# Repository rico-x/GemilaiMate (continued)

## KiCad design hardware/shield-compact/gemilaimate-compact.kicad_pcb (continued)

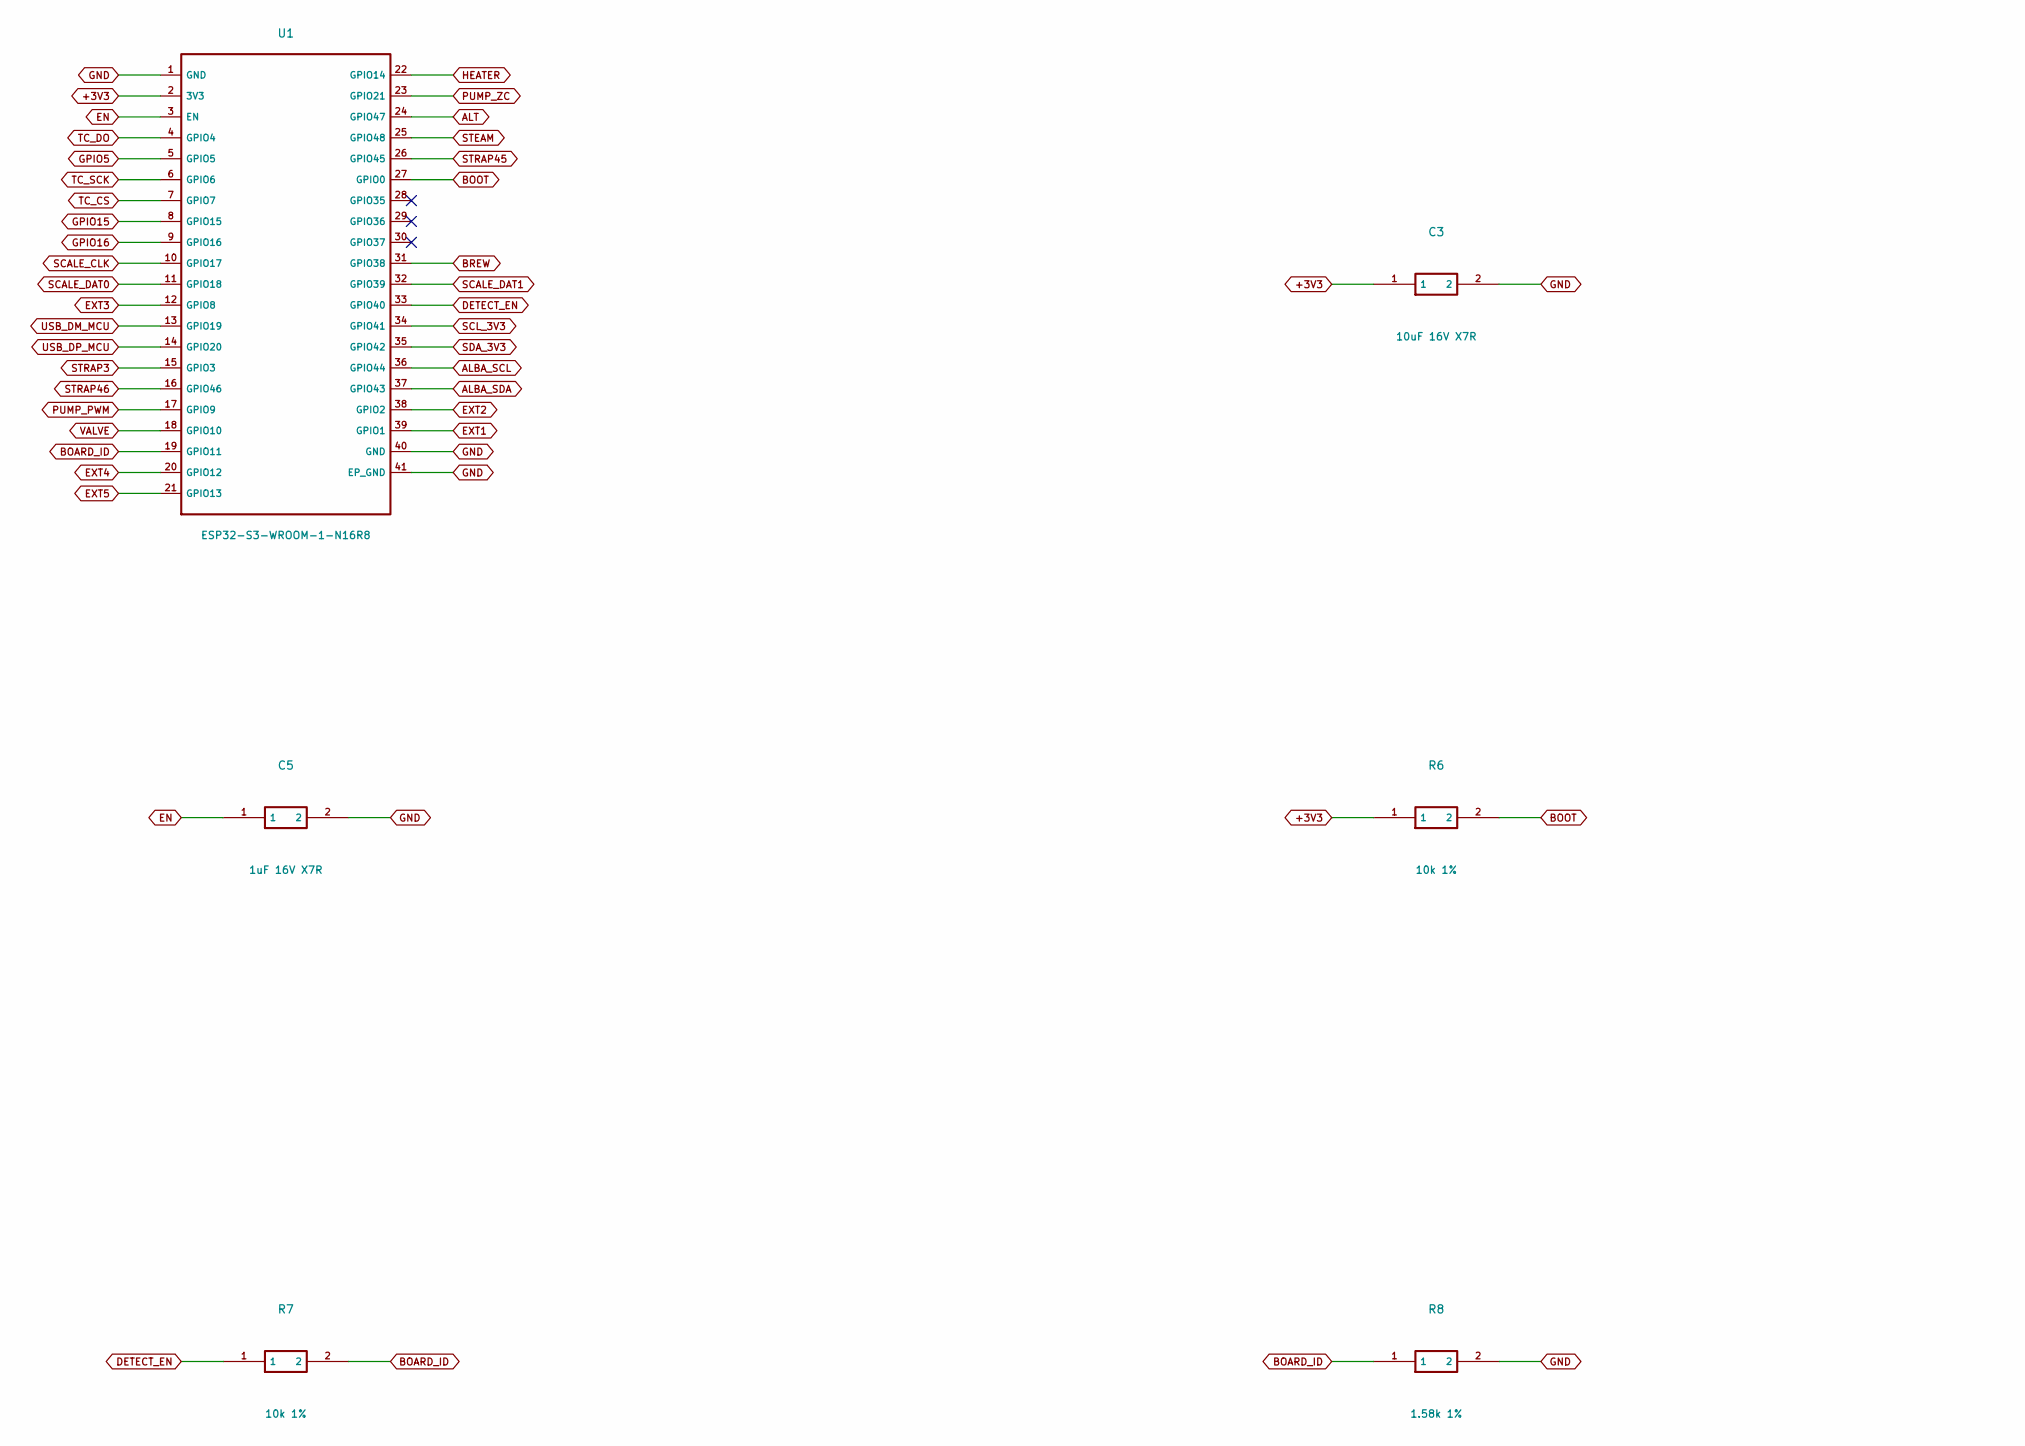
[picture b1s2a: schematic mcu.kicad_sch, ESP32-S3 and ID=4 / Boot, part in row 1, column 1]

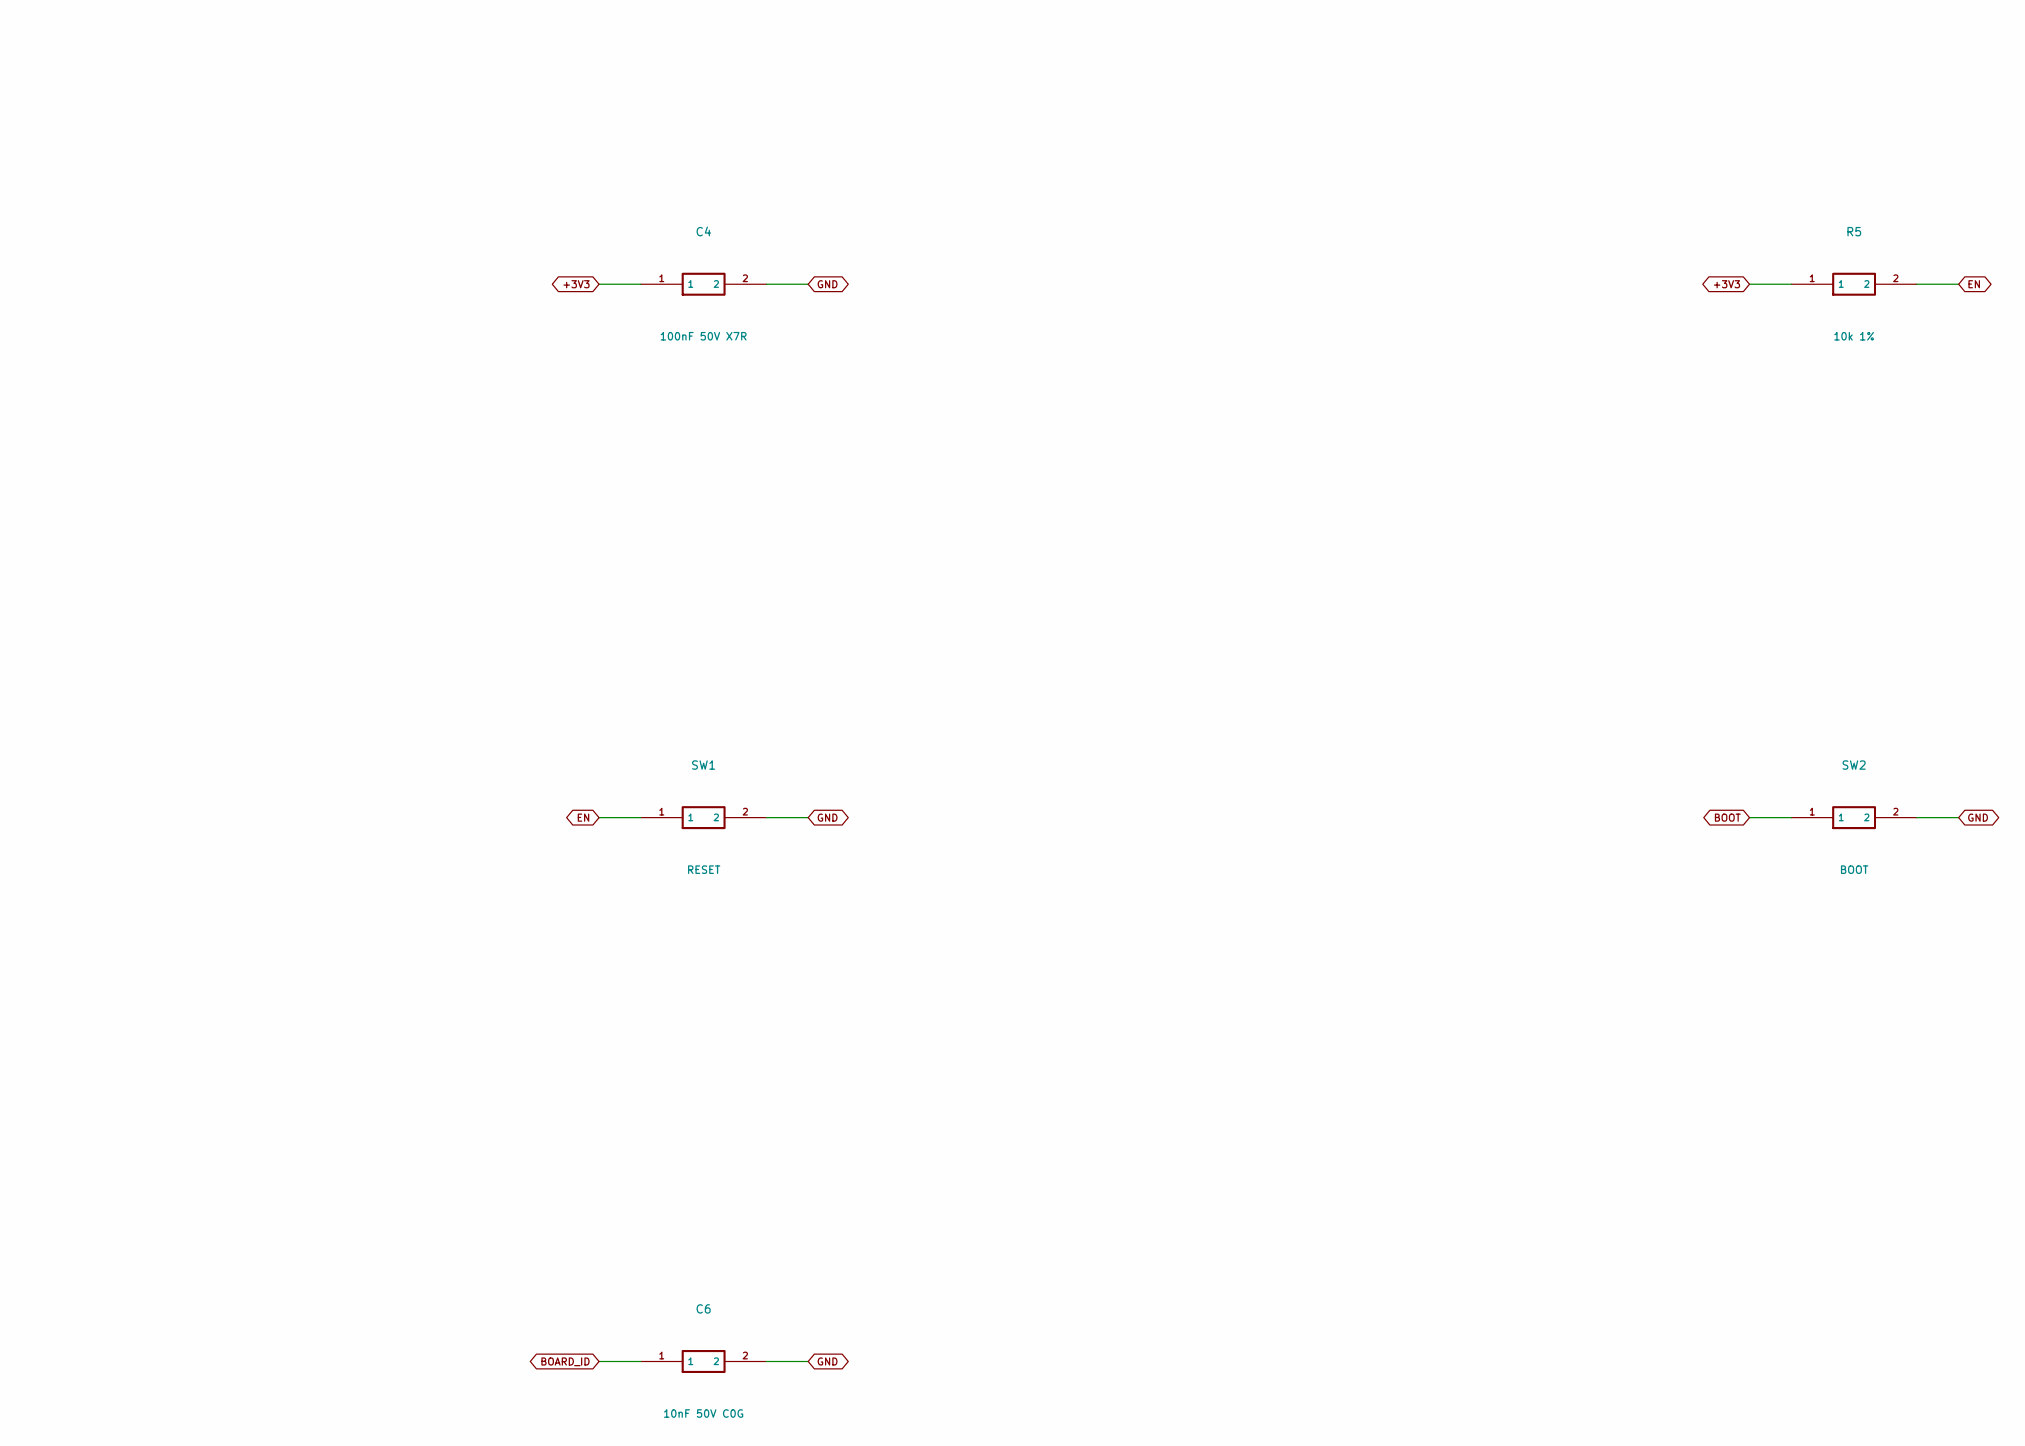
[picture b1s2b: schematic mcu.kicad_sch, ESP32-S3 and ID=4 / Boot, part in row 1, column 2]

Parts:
C3: 10uF 16V X7R; C_1206_3216Metric_Pad1.33x1.80mm_HandSolder
C4: 100nF 50V X7R; C_0805_2012Metric_Pad1.18x1.45mm_HandSolder
C5: 1uF 16V X7R; C_0805_2012Metric_Pad1.18x1.45mm_HandSolder
C6: 10nF 50V C0G; C_0805_2012Metric_Pad1.18x1.45mm_HandSolder
R5, R6, R7: 10k 1%; R_0805_2012Metric_Pad1.20x1.40mm_HandSolder
R8: 1.58k 1%; R_0805_2012Metric_Pad1.20x1.40mm_HandSolder
SW1: RESET; SW_SPST_TL3342
SW2: BOOT; SW_SPST_TL3342
U1: ESP32-S3-WROOM-1-N16R8; ESP32-S3-WROOM-1

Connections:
+3V3: C3.1, C4.1, R5.1, R6.1, U1.2 (3V3); also elsewhere on the board
ALBA_SCL: U1.36 (GPIO44); also elsewhere on the board
ALBA_SDA: U1.37 (GPIO43); also elsewhere on the board
ALT: U1.24 (GPIO47); also elsewhere on the board
BOARD_ID: C6.1, R7.2, R8.1, U1.19 (GPIO11)
BOOT: R6.2, SW2.1, U1.27 (GPIO0); also elsewhere on the board
BREW: U1.31 (GPIO38); also elsewhere on the board
DETECT_EN: R7.1, U1.33 (GPIO40)
EN: C5.1, R5.2, SW1.1, U1.3 (EN)
EXT1: U1.39 (GPIO1); also elsewhere on the board
EXT2: U1.38 (GPIO2); also elsewhere on the board
EXT3: U1.12 (GPIO8); also elsewhere on the board
EXT4: U1.20 (GPIO12); also elsewhere on the board
EXT5: U1.21 (GPIO13); also elsewhere on the board
GND: C3.2, C4.2, C5.2, C6.2, R8.2, SW1.2, SW2.2, U1.1 (GND), U1.40 (GND), U1.41 (EP_GND); also elsewhere on the board
GPIO5: U1.5 (GPIO5); also elsewhere on the board
GPIO15: U1.8 (GPIO15); also elsewhere on the board
GPIO16: U1.9 (GPIO16); also elsewhere on the board
HEATER: U1.22 (GPIO14); also elsewhere on the board
PUMP_PWM: U1.17 (GPIO9); also elsewhere on the board
PUMP_ZC: U1.23 (GPIO21); also elsewhere on the board
SCALE_CLK: U1.10 (GPIO17); also elsewhere on the board
SCALE_DAT0: U1.11 (GPIO18); also elsewhere on the board
SCALE_DAT1: U1.32 (GPIO39); also elsewhere on the board
SCL_3V3: U1.34 (GPIO41); also elsewhere on the board
SDA_3V3: U1.35 (GPIO42); also elsewhere on the board
STEAM: U1.25 (GPIO48); also elsewhere on the board
STRAP3: U1.15 (GPIO3); also elsewhere on the board
STRAP45: U1.26 (GPIO45); also elsewhere on the board
STRAP46: U1.16 (GPIO46); also elsewhere on the board
TC_CS: U1.7 (GPIO7); also elsewhere on the board
TC_DO: U1.4 (GPIO4); also elsewhere on the board
TC_SCK: U1.6 (GPIO6); also elsewhere on the board
USB_DM_MCU: U1.13 (GPIO19); also elsewhere on the board
USB_DP_MCU: U1.14 (GPIO20); also elsewhere on the board
VALVE: U1.18 (GPIO10); also elsewhere on the board

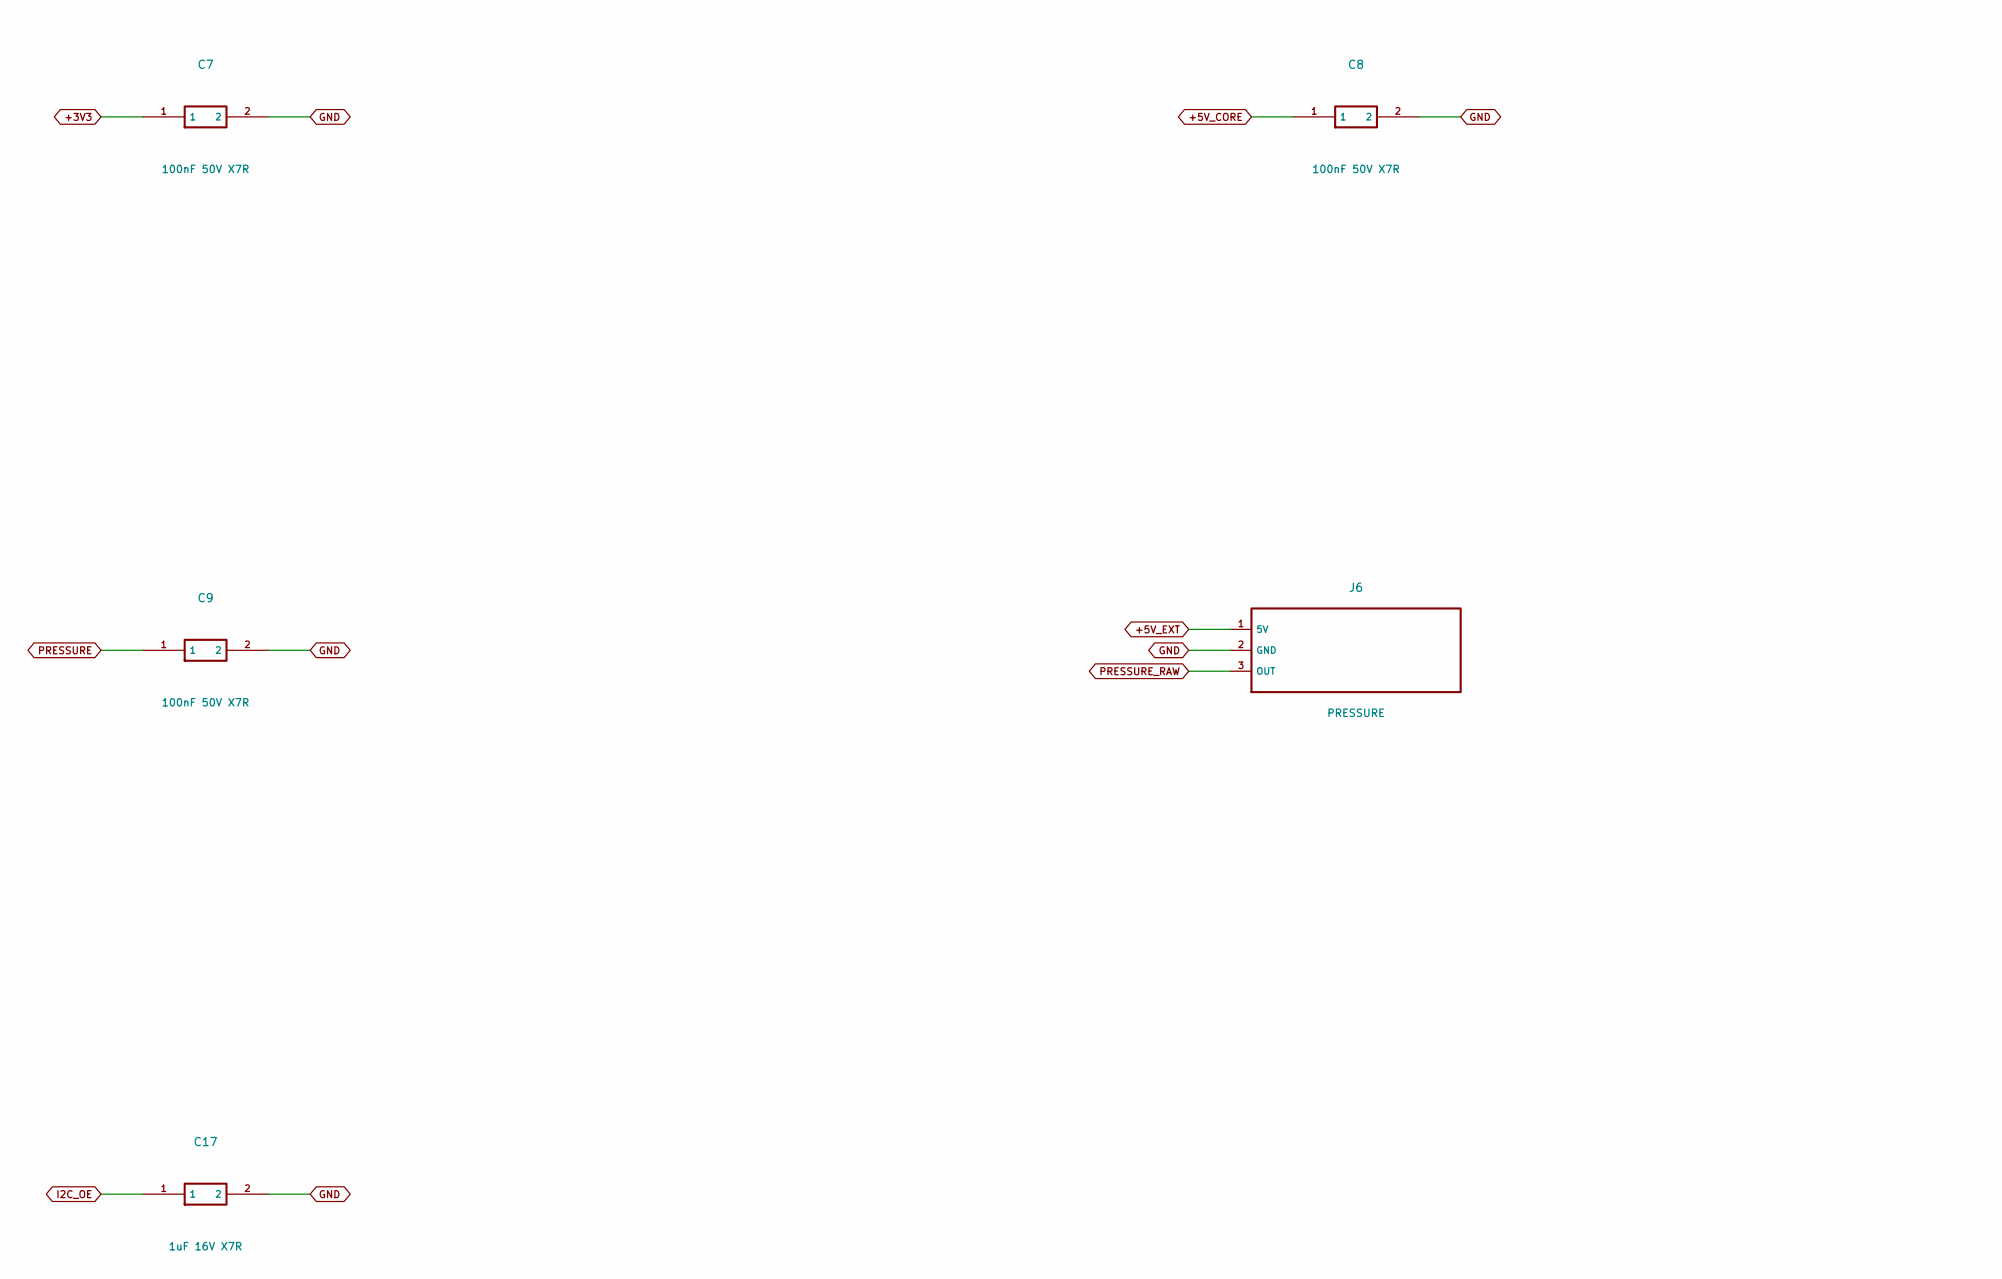
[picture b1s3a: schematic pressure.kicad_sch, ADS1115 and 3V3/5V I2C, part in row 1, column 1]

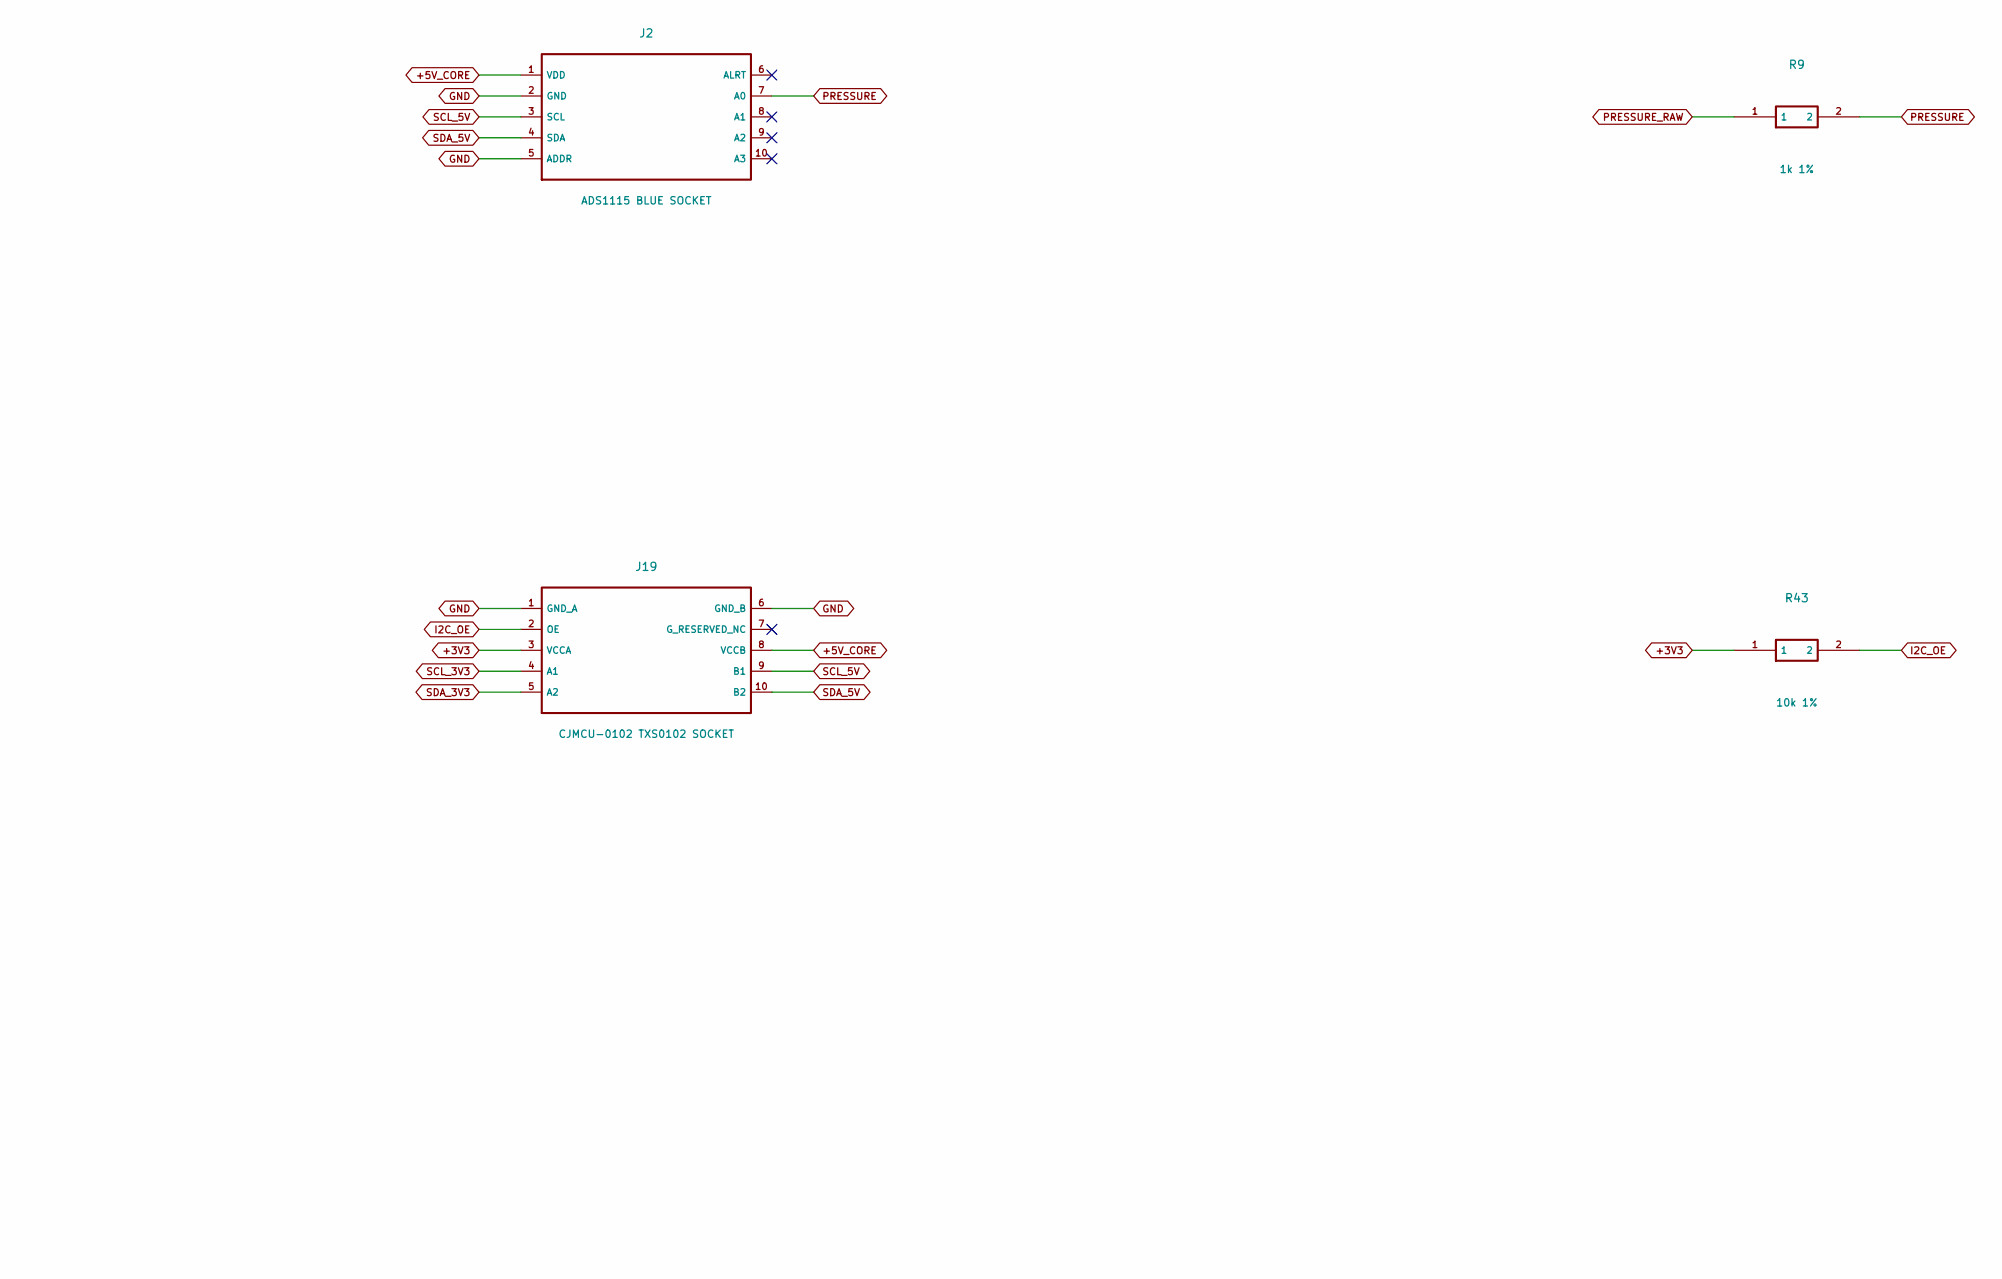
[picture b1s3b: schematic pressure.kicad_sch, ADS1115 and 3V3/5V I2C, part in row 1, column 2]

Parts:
C7, C8, C9: 100nF 50V X7R; C_0805_2012Metric_Pad1.18x1.45mm_HandSolder
C17: 1uF 16V X7R; C_0805_2012Metric_Pad1.18x1.45mm_HandSolder
J2: ADS1115 BLUE SOCKET; ADS1115_socket
J6: PRESSURE; JST_PH_B3B-PH-K_1x03_P2.00mm_Vertical
J19: CJMCU-0102 TXS0102 SOCKET; CJMCU0102_socket
R9: 1k 1%; R_0805_2012Metric_Pad1.20x1.40mm_HandSolder
R43: 10k 1%; R_0805_2012Metric_Pad1.20x1.40mm_HandSolder

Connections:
+3V3: C7.1, J19.3 (VCCA), R43.1; also elsewhere on the board
+5V_CORE: C8.1, J2.1 (VDD), J19.8 (VCCB); also elsewhere on the board
+5V_EXT: J6.1 (5V); also elsewhere on the board
GND: C7.2, C8.2, C9.2, C17.2, J2.2 (GND), J2.5 (ADDR), J6.2 (GND), J19.1 (GND_A), J19.6 (GND_B); also elsewhere on the board
I2C_OE: C17.1, J19.2 (OE), R43.2
PRESSURE: C9.1, J2.7 (A0), R9.2
PRESSURE_RAW: J6.3 (OUT), R9.1
SCL_3V3: J19.4 (A1); also elsewhere on the board
SCL_5V: J2.3 (SCL), J19.9 (B1)
SDA_3V3: J19.5 (A2); also elsewhere on the board
SDA_5V: J2.4 (SDA), J19.10 (B2)

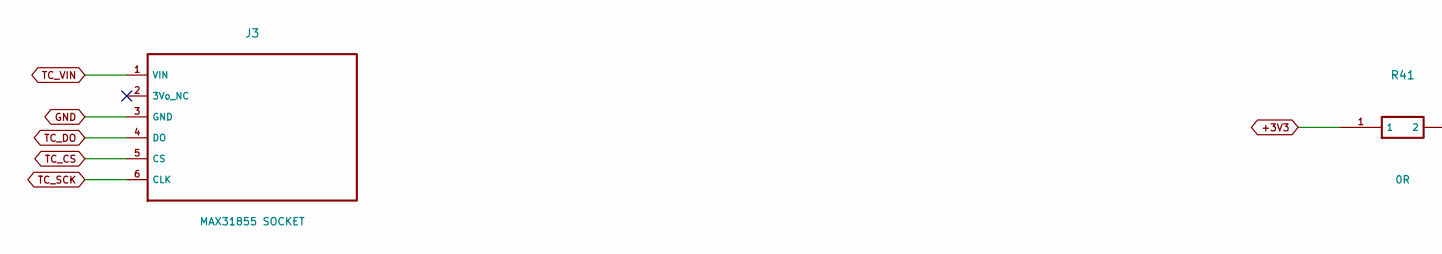
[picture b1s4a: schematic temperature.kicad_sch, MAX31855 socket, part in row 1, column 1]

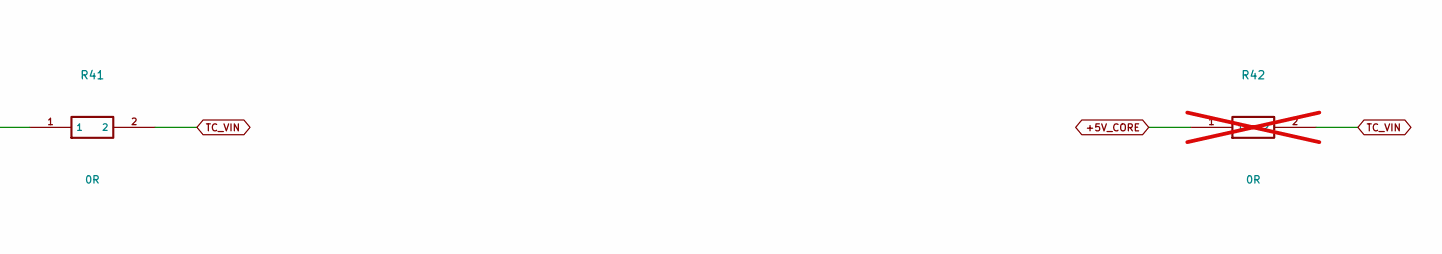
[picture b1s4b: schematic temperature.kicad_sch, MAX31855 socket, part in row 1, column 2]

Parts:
J3: MAX31855 SOCKET; MAX31855_socket
R41: 0R; R_0805_2012Metric_Pad1.20x1.40mm_HandSolder
R42: 0R; R_0805_2012Metric_Pad1.20x1.40mm_HandSolder; not fitted

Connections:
+3V3: R41.1; also elsewhere on the board
+5V_CORE: R42.1; also elsewhere on the board
GND: J3.3 (GND); also elsewhere on the board
TC_CS: J3.5 (CS); also elsewhere on the board
TC_DO: J3.4 (DO); also elsewhere on the board
TC_SCK: J3.6 (CLK); also elsewhere on the board
TC_VIN: J3.1 (VIN), R41.2, R42.2

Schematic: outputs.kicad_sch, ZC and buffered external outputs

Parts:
C10, C11, C12, C15: 100nF 50V X7R; C_0805_2012Metric_Pad1.18x1.45mm_HandSolder
J8: ROBOTDYN; JST_PH_B6B-PH-K_1x06_P2.00mm_Vertical
J9: VALVE SSR; JST_PH_B3B-PH-K_1x03_P2.00mm_Vertical
J10: HEATER UNUSED; JST_PH_B3B-PH-K_1x03_P2.00mm_Vertical; not fitted
J11: ALT SSR; JST_PH_B3B-PH-K_1x03_P2.00mm_Vertical
Q1: MMBT3904; SOT-23_Handsoldering
R10, R14, R15, R16, R17, R18, R19, R20, R21, R22: 10k 1%; R_0805_2012Metric_Pad1.20x1.40mm_HandSolder
R11: 1k 1%; R_0805_2012Metric_Pad1.20x1.40mm_HandSolder
R12: 47k 1%; R_0805_2012Metric_Pad1.20x1.40mm_HandSolder
R13, R36, R38: 100k 1%; R_0805_2012Metric_Pad1.20x1.40mm_HandSolder
R27, R28: 0R; R_0805_2012Metric_Pad1.20x1.40mm_HandSolder
R29, R30: 4.7k 1%; R_0805_2012Metric_Pad1.20x1.40mm_HandSolder
R31, R32, R33, R34: 180R 1%; R_0805_2012Metric_Pad1.20x1.40mm_HandSolder
R35, R37: 100R 1%; R_0805_2012Metric_Pad1.20x1.40mm_HandSolder
U4: SN74LVC1G17DBVR; SOT-23-5_HandSoldering
U5: SN74LVC1G125DBVR; SOT-23-5_HandSoldering
U6: SN74AHCT125DR; SOIC-14_3.9x8.7mm_P1.27mm

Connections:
+3V3: C10.1, C12.1, C15.1, R14.1, R29.1, R30.1, U4.5 (VCC), U5.5 (VCC); also elsewhere on the board
+5V_EXT: C11.1, J8.1 (5V), J9.1 (5V), J10.1 (5V), J11.1 (5V), R10.1, R12.1, U6.13 (4OE_N), U6.14 (VCC); also elsewhere on the board
ALBA_SCL: R27.1, R30.2; also elsewhere on the board
ALBA_SDA: R28.1, R29.2; also elsewhere on the board
ALT: R18.1, U6.9 (3A); also elsewhere on the board
ALT_5V: J11.3 (IN), R22.1, U6.8 (3Y)
EXT_BASE: Q1.1 (B), R12.2, R13.1
GND: C10.2, C11.2, C12.2, C15.2, J8.2 (GND), J9.2 (GND), J10.2 (GND), J11.2 (GND), Q1.2 (E), R13.2, R15.2, R16.2, R17.2, R18.2, R19.2, R20.2, R21.2, R22.2, R36.2, R38.2, U4.3 (GND), U5.3 (GND), U6.7 (GND), U6.12 (4A); also elsewhere on the board
HEATER: R17.1, U6.5 (2A); also elsewhere on the board
HEATER_5V: J10.3 (IN), R21.1, U6.6 (2Y)
LED_GATE4: R35.2, R36.1; also elsewhere on the board
LED_GATE5: R37.2, R38.1; also elsewhere on the board
OUTPUT_OE_N: Q1.3 (C), R14.2, U5.1 (OE_N), U6.1 (1OE_N), U6.4 (2OE_N), U6.10 (3OE_N)
PCA_LED0: R31.1; also elsewhere on the board
PCA_LED1: R32.1; also elsewhere on the board
PCA_LED2: R33.1; also elsewhere on the board
PCA_LED3: R34.1; also elsewhere on the board
PCA_LED4: R35.1; also elsewhere on the board
PCA_LED5: R37.1; also elsewhere on the board
PCA_SCL: R27.2; also elsewhere on the board
PCA_SDA: R28.2; also elsewhere on the board
PUMP_OUT: J8.4 (PSM), R19.1, U5.4 (Y)
PUMP_PWM: R15.1, U5.2 (A); also elsewhere on the board
PUMP_ZC: U4.4 (Y); also elsewhere on the board
RGBW0: R31.2; also elsewhere on the board
RGBW1: R32.2; also elsewhere on the board
RGBW2: R33.2; also elsewhere on the board
RGBW3: R34.2; also elsewhere on the board
VALVE: R16.1, U6.2 (1A); also elsewhere on the board
VALVE_5V: J9.3 (IN), R20.1, U6.3 (1Y)
ZC_IN: R11.2, U4.2 (A)
ZC_RAW: J8.3 (ZC), R10.2, R11.1

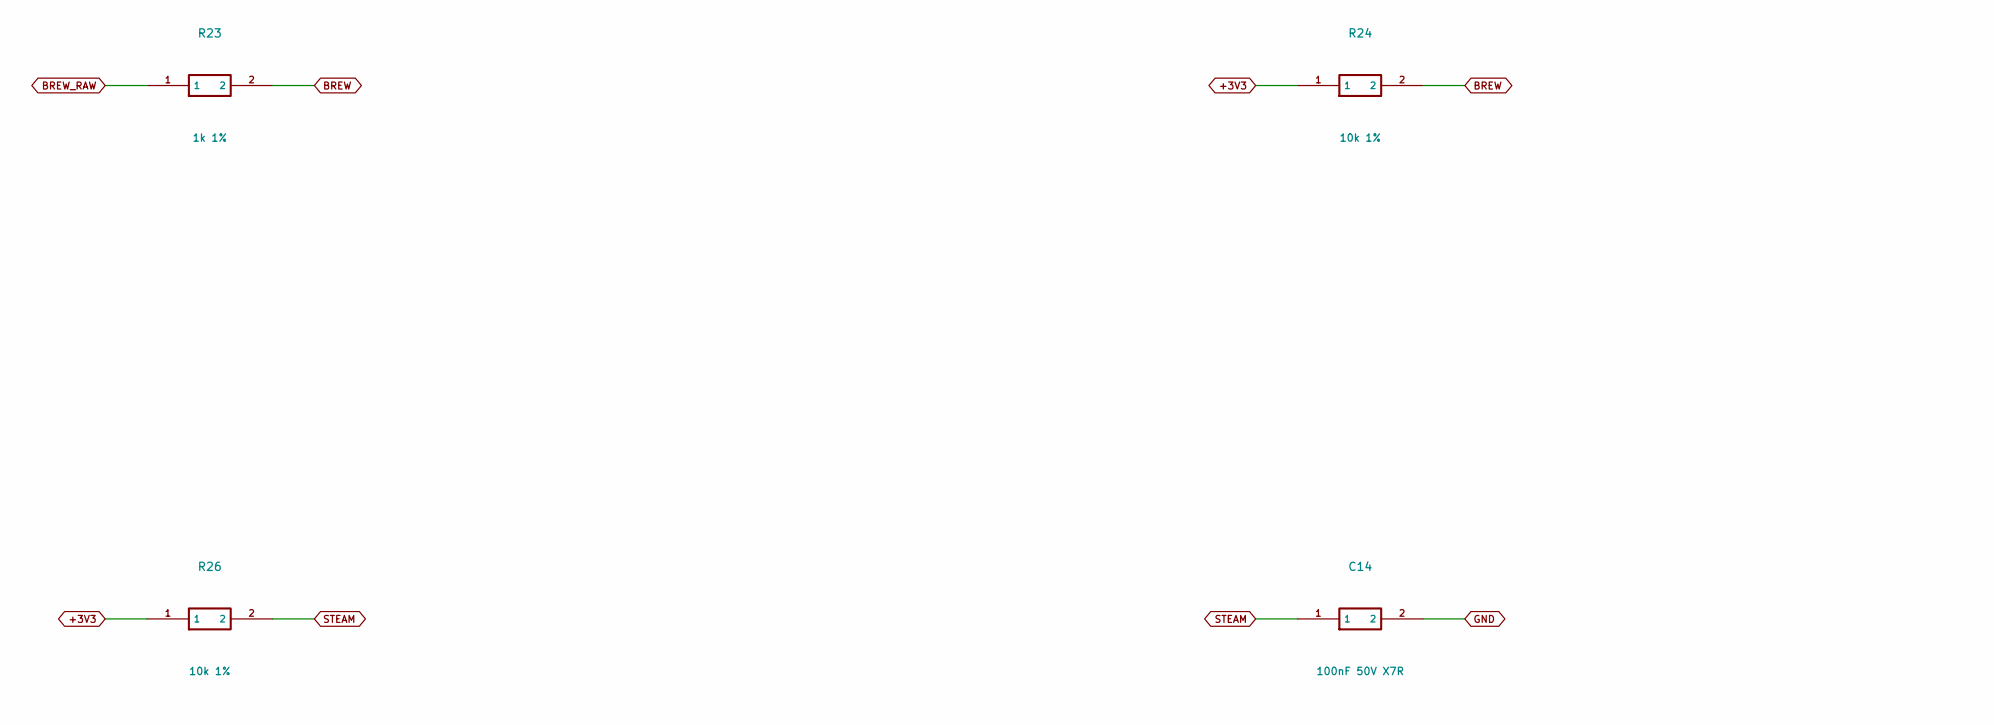
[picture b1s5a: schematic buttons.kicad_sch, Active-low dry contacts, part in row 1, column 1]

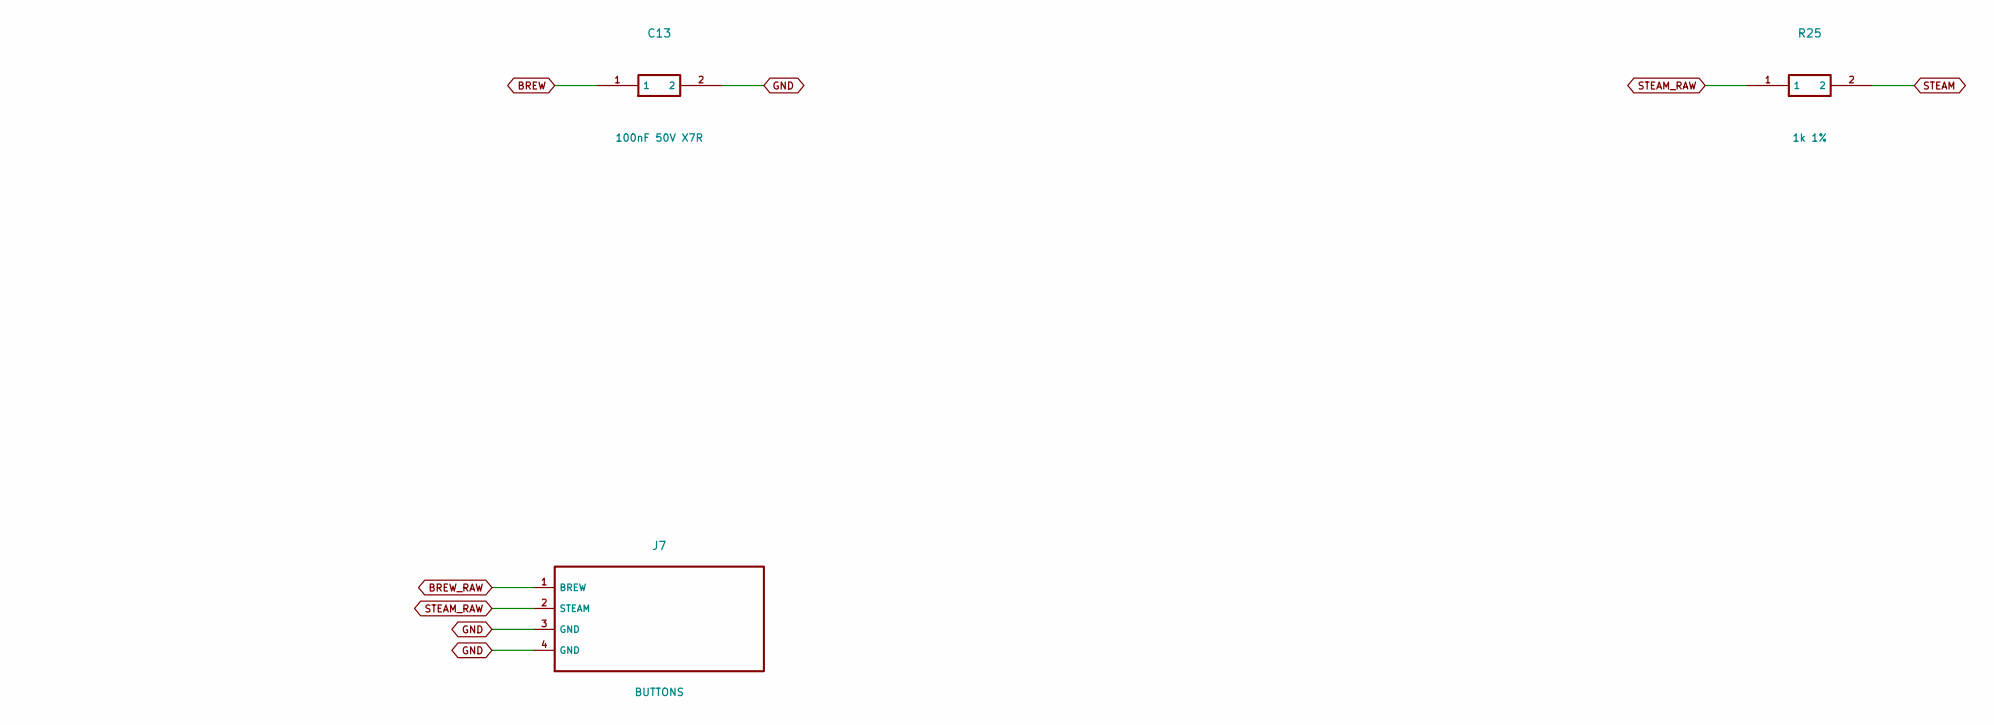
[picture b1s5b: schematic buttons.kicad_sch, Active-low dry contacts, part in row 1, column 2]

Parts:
C13, C14: 100nF 50V X7R; C_0805_2012Metric_Pad1.18x1.45mm_HandSolder
J7: BUTTONS; JST_PH_B4B-PH-K_1x04_P2.00mm_Vertical
R23, R25: 1k 1%; R_0805_2012Metric_Pad1.20x1.40mm_HandSolder
R24, R26: 10k 1%; R_0805_2012Metric_Pad1.20x1.40mm_HandSolder

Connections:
+3V3: R24.1, R26.1; also elsewhere on the board
BREW: C13.1, R23.2, R24.2; also elsewhere on the board
BREW_RAW: J7.1 (BREW), R23.1
GND: C13.2, C14.2, J7.3 (GND), J7.4 (GND); also elsewhere on the board
STEAM: C14.1, R25.2, R26.2; also elsewhere on the board
STEAM_RAW: J7.2 (STEAM), R25.1
